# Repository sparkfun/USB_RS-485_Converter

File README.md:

SparkFun USB to RS-485 Converter
========================================

[*SparkFun USB to RS-485 Converter (BOB-09822)*](https://www.sparkfun.com/products/9822)

This breakout board pairs an SP3485 RS-485 transceiver with an FT232RL USB UART IC to convert a USB stream to RS-485.

Repository Contents
-------------------

* **/Hardware** - Eagle design files (.brd, .sch)
* **/Production** - Production panel files (.brd)

Documentation
--------------
* **[SparkFun Fritzing repo](https://github.com/sparkfun/Fritzing_Parts)** - Fritzing diagrams for SparkFun products.
* **[SparkFun 3D Model repo](https://github.com/sparkfun/3D_Models)** - 3D models of SparkFun products. 

License Information
-------------------
This product is _**open source**_! 

The **hardware** is released under [Creative Commons ShareAlike 4.0 International](https://creativecommons.org/licenses/by-sa/4.0/).

Please use, reuse, and modify these files as you see fit. Please maintain attribution to SparkFun Electronics and release anything derivative under the same license.

Distributed as-is; no warranty is given.

- Your friends at SparkFun.

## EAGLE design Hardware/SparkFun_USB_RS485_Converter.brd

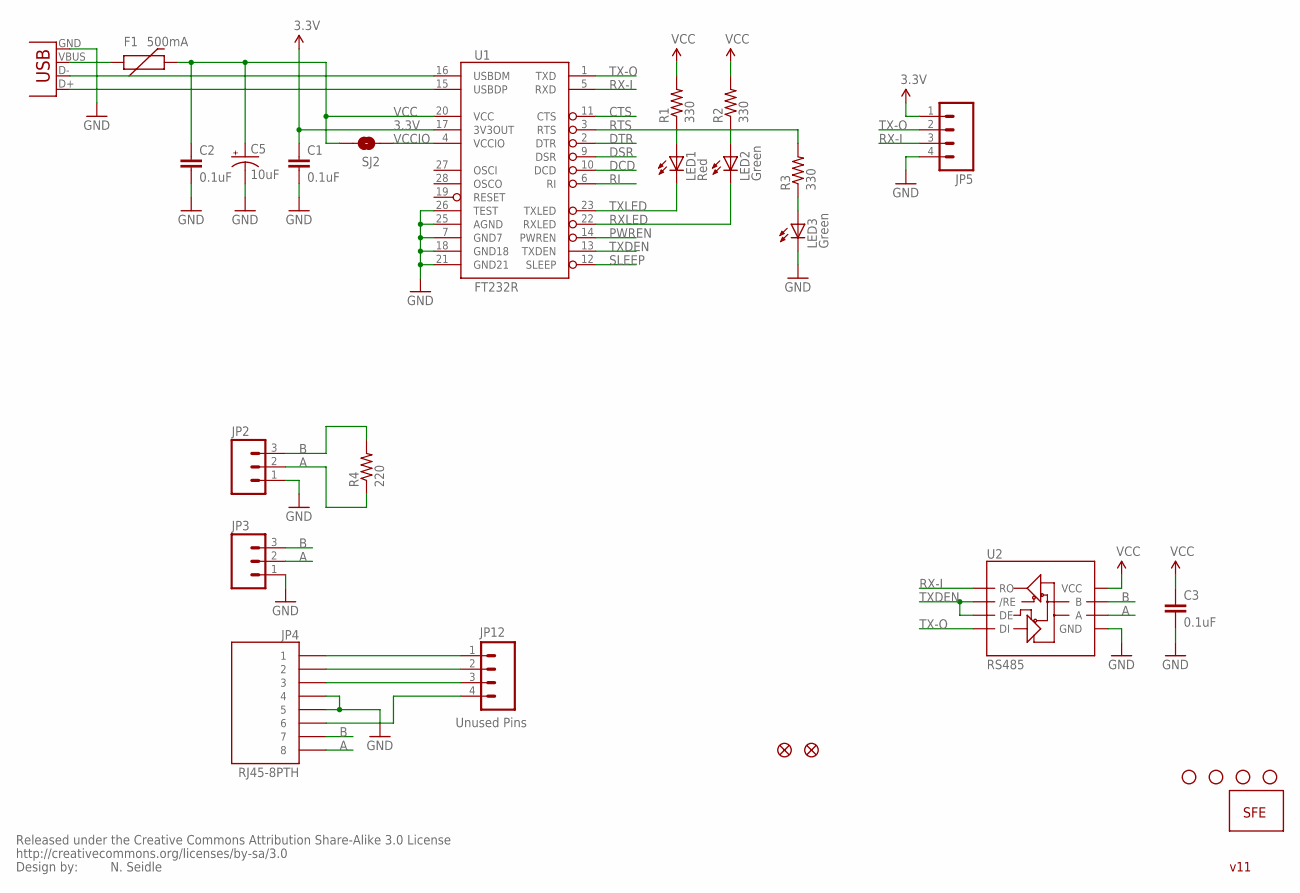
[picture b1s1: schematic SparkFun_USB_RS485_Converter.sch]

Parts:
C1, C2, C3: 0.1uF; 0402-CAP
C5: 10uF; EIA3216
F1: 500mA; PTC-1206
JP1, JP6, JP7, JP8: STAND-OFF
JP2: M03SCREW; SCREWTERMINAL-3.5MM-3
JP3: M03PTH; 1X03
JP4: RJ45-8PTH; RJ45-8
JP5: M04PTH; 1X04
JP9, JP10: FIDUCIAL1X2; FIDUCIAL-1X2
JP12: Unused Pins; 1X04
LED1: Red; LED-0603
LED2, LED3: Green; LED-0603
R1, R2, R3: 330; 0402-RES
R4: 220; 0402-RES
SJ2: SOLDERJUMPERNC2; SJ_2S-NOTRACE
U1: FT232R; SSOP28DB
U2: RS485; SO08
U$1: CREATIVE_COMMONS
U$2: LOGO-SFENEW; SFE-NEW-WEBLOGO
X2: USBSMD; USB-MINIB

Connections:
3.3V: C1.1, JP5.1, U1.17 (3V3OUT)
A: JP2.2, JP3.2, JP4.8, R4.1, U2.6 (A)
B: JP2.3, JP3.3, JP4.7, R4.2, U2.7 (B)
CTS: U1.11 (CTS)
DCD: U1.10 (DCD)
DSR: U1.9 (DSR)
DTR: U1.2 (DTR)
GND: C1.2, C2.2, C3.2, C5.C (-), JP2.1, JP3.1, JP4.4, JP4.5, JP5.4, LED3.C, U1.7 (GND7), U1.18 (GND18), U1.21 (GND21), U1.25 (AGND), U1.26 (TEST), U2.5 (GND), X2.GND
unnamed: LED1.A, R1.1
unnamed: LED2.A, R2.1
unnamed: F1.1, X2.VBUS
unnamed: LED3.A, R3.1
unnamed: JP4.1, JP12.1
unnamed: JP4.2, JP12.2
unnamed: JP4.3, JP12.3
unnamed: JP4.6, JP12.4
PWREN: U1.14 (PWREN)
RI: U1.6 (RI)
RTS: R3.2, U1.3 (RTS)
RX-I: JP5.3, U1.5 (RXD), U2.1 (RO)
RXLED: LED2.C, U1.22 (RXLED)
SLEEP: U1.12 (SLEEP)
TX-O: JP5.2, U1.1 (TXD), U2.4 (DI)
TXDEN: U1.13 (TXDEN), U2.2 (/RE), U2.3 (DE)
TXLED: LED1.C, U1.23 (TXLED)
USB_D+: U1.15 (USBDP), X2.D+
USB_D-: U1.16 (USBDM), X2.D-
VCC: C2.1, C3.1, C5.A (+), F1.2, R1.2, R2.2, SJ2.2, U1.20 (VCC), U2.8 (VCC)
VCCIO: SJ2.1, U1.4 (VCCIO)

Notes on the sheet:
N. Seidle
v11

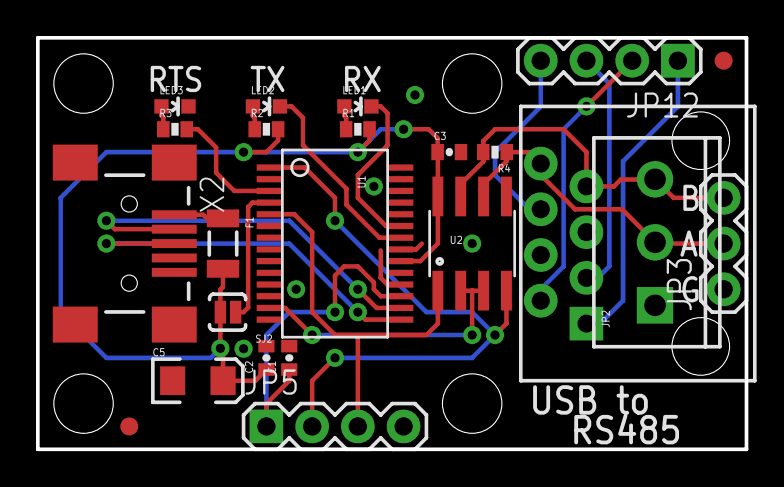
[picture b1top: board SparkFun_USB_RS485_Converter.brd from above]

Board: 2 copper layers, 39.4 x 22.9 mm, 29 parts (1 on the bottom side), 22 nets.

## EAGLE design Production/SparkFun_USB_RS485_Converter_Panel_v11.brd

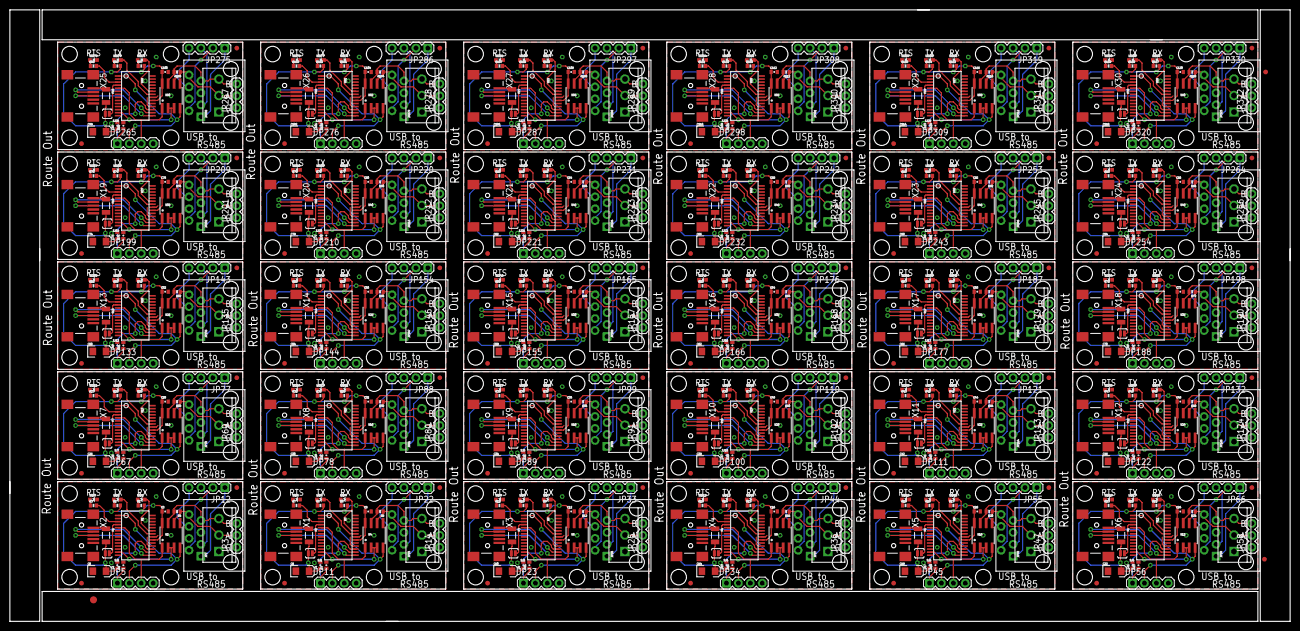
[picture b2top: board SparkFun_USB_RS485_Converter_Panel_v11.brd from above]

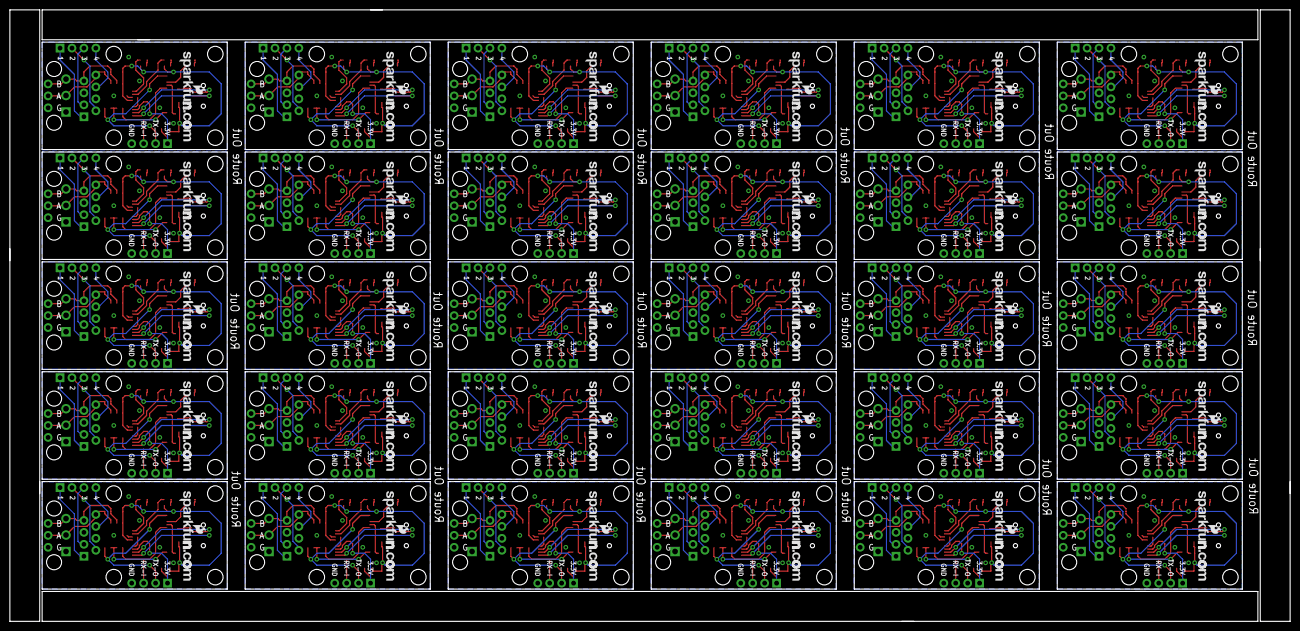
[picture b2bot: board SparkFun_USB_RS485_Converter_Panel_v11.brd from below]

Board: 2 copper layers, 272.3 x 130.0 mm, 843 parts (30 on the bottom side), 660 nets.

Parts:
C1, C2, C3, C4, C7, C8, C9, C11, C12, C13, C15, C16, C17, C19, C20, C21, C23, C24, C25, C27, C28, C29, C31, C32, C33, C35, C36, C37, C39, C40, C41, C43, C44, C45, C47, C48, C49, C51, C52, C53, C55, C56, C57, C59, C60, C61, C63, C64, C65, C67, C68, C69, C71, C72, C73, C75, C76, C77, C79, C80, C81, C83, C84, C85, C87, C88, C89, C91, C92, C93, C95, C96, C97, C99, C100, C101, C103, C104, C105, C107, C108, C109, C111, C112, C113, C115, C116, C117, C119, C120: 0.1uF; 0402-CAP
C5, C6, C10, C14, C18, C22, C26, C30, C34, C38, C42, C46, C50, C54, C58, C62, C66, C70, C74, C78, C82, C86, C90, C94, C98, C102, C106, C110, C114, C118: 10uF; EIA3216
E$1: FIDUCIAL-1.5X3
E$5, E$6: FIDUCIAL-1X2
F1, F2, F3, F4, F5, F6, F7, F8, F9, F10, F11, F12, F13, F14, F15, F16, F17, F18, F19, F20, F21, F22, F23, F24, F25, F26, F27, F28, F29, F30: 500mA; PTC-1206
JP1, JP6, JP7, JP8, JP16, JP17, JP18, JP19, JP27, JP28, JP29, JP30, JP38, JP39, JP40, JP41, JP49, JP50, JP51, JP52, JP60, JP61, JP62, JP63, JP71, JP72, JP73, JP74, JP82, JP83, JP84, JP85, JP93, JP94, JP95, JP96, JP104, JP105, JP106, JP107, JP115, JP116, JP117, JP118, JP126, JP127, JP128, JP129, JP137, JP138, JP139, JP140, JP148, JP149, JP150, JP151, JP159, JP160, JP161, JP162, JP170, JP171, JP172, JP173, JP181, JP182, JP183, JP184, JP192, JP193, JP194, JP195, JP203, JP204, JP205, JP206, JP214, JP215, JP216, JP217, JP225, JP226, JP227, JP228, JP236, JP237, JP238, JP239, JP247, JP248, JP249, JP250, JP258, JP259, JP260, JP261, JP269, JP270, JP271, JP272, JP280, JP281, JP282, JP283, JP291, JP292, JP293, JP294, JP302, JP303, JP304, JP305, JP313, JP314, JP315, JP316, JP324, JP325, JP326, JP327: STAND-OFF
JP2, JP15, JP26, JP37, JP48, JP59, JP70, JP81, JP92, JP103, JP114, JP125, JP136, JP147, JP158, JP169, JP180, JP191, JP202, JP213, JP224, JP235, JP246, JP257, JP268, JP279, JP290, JP301, JP312, JP323: SCREWTERMINAL-3.5MM-3
JP3, JP14, JP25, JP36, JP47, JP58, JP69, JP80, JP91, JP102, JP113, JP124, JP135, JP146, JP157, JP168, JP179, JP190, JP201, JP212, JP223, JP234, JP245, JP256, JP267, JP278, JP289, JP300, JP311, JP322: 1X03
JP4, JP13, JP24, JP35, JP46, JP57, JP68, JP79, JP90, JP101, JP112, JP123, JP134, JP145, JP156, JP167, JP178, JP189, JP200, JP211, JP222, JP233, JP244, JP255, JP266, JP277, JP288, JP299, JP310, JP321: RJ45-8PTH; RJ45-8
JP5, JP11, JP23, JP34, JP45, JP56, JP67, JP78, JP89, JP100, JP111, JP122, JP133, JP144, JP155, JP166, JP177, JP188, JP199, JP210, JP221, JP232, JP243, JP254, JP265, JP276, JP287, JP298, JP309, JP320: 1X04
JP9, JP10, JP20, JP21, JP31, JP32, JP42, JP43, JP53, JP54, JP64, JP65, JP75, JP76, JP86, JP87, JP97, JP98, JP108, JP109, JP119, JP120, JP130, JP131, JP141, JP142, JP152, JP153, JP163, JP164, JP174, JP175, JP185, JP186, JP196, JP197, JP207, JP208, JP218, JP219, JP229, JP230, JP240, JP241, JP251, JP252, JP262, JP263, JP273, JP274, JP284, JP285, JP295, JP296, JP306, JP307, JP317, JP318, JP328, JP329: FIDUCIAL1X2; FIDUCIAL-1X2
JP12, JP22, JP33, JP44, JP55, JP66, JP77, JP88, JP99, JP110, JP121, JP132, JP143, JP154, JP165, JP176, JP187, JP198, JP209, JP220, JP231, JP242, JP253, JP264, JP275, JP286, JP297, JP308, JP319, JP330: Unused Pins; 1X04
LED1, LED4, LED7, LED10, LED13, LED16, LED19, LED22, LED25, LED28, LED31, LED34, LED37, LED40, LED43, LED46, LED49, LED52, LED55, LED58, LED61, LED64, LED67, LED70, LED73, LED76, LED79, LED82, LED85, LED88: Red; LED-0603
LED2, LED3, LED5, LED6, LED8, LED9, LED11, LED12, LED14, LED15, LED17, LED18, LED20, LED21, LED23, LED24, LED26, LED27, LED29, LED30, LED32, LED33, LED35, LED36, LED38, LED39, LED41, LED42, LED44, LED45, LED47, LED48, LED50, LED51, LED53, LED54, LED56, LED57, LED59, LED60, LED62, LED63, LED65, LED66, LED68, LED69, LED71, LED72, LED74, LED75, LED77, LED78, LED80, LED81, LED83, LED84, LED86, LED87, LED89, LED90: Green; LED-0603
R1, R2, R3, R5, R6, R7, R9, R10, R11, R13, R14, R15, R17, R18, R19, R21, R22, R23, R25, R26, R27, R29, R30, R31, R33, R34, R35, R37, R38, R39, R41, R42, R43, R45, R46, R47, R49, R50, R51, R53, R54, R55, R57, R58, R59, R61, R62, R63, R65, R66, R67, R69, R70, R71, R73, R74, R75, R77, R78, R79, R81, R82, R83, R85, R86, R87, R89, R90, R91, R93, R94, R95, R97, R98, R99, R101, R102, R103, R105, R106, R107, R109, R110, R111, R113, R114, R115, R117, R118, R119: 330; 0402-RES
R4, R8, R12, R16, R20, R24, R28, R32, R36, R40, R44, R48, R52, R56, R60, R64, R68, R72, R76, R80, R84, R88, R92, R96, R100, R104, R108, R112, R116, R120: 220; 0402-RES
SJ1, SJ2, SJ3, SJ4, SJ5, SJ6, SJ7, SJ8, SJ9, SJ10, SJ11, SJ12, SJ13, SJ14, SJ15, SJ16, SJ17, SJ18, SJ19, SJ20, SJ21, SJ22, SJ23, SJ24, SJ25, SJ26, SJ27, SJ28, SJ29, SJ30: SOLDERJUMPERNC2; SJ_2S-NOTRACE
U1, U3, U5, U7, U9, U11, U13, U15, U17, U19, U21, U23, U25, U27, U29, U31, U33, U35, U37, U39, U41, U43, U45, U47, U49, U51, U53, U55, U57, U59: FT232R; SSOP28DB
U2, U4, U6, U8, U10, U12, U14, U16, U18, U20, U22, U24, U26, U28, U30, U32, U34, U36, U38, U40, U42, U44, U46, U48, U50, U52, U54, U56, U58, U60: RS485; SO08
U$1, U$2, U$3, U$4, U$5, U$6, U$7, U$8, U$9, U$10, U$11, U$12, U$13, U$14, U$15, U$16, U$17, U$18, U$19, U$20, U$21, U$22, U$23, U$24, U$25, U$26, U$27, U$28, U$29, U$30: LOGO-SFENEW; SFE-NEW-WEBLOGO
X1, X2, X3, X4, X5, X6, X7, X8, X9, X10, X11, X12, X13, X14, X15, X16, X17, X18, X19, X20, X21, X22, X23, X24, X25, X26, X27, X28, X29, X30: USBSMD; USB-MINIB

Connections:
3.3V: C1.1, JP5.1, U1.17
3.3V1: C7.1, JP11.1, U3.17
3.3V2: C11.1, JP23.1, U5.17
3.3V3: C15.1, JP34.1, U7.17
3.3V4: C19.1, JP45.1, U9.17
3.3V5: C23.1, JP56.1, U11.17
3.3V6: C27.1, JP67.1, U13.17
3.3V7: C31.1, JP78.1, U15.17
3.3V8: C35.1, JP89.1, U17.17
3.3V9: C39.1, JP100.1, U19.17
3.3V10: C43.1, JP111.1, U21.17
3.3V11: C47.1, JP122.1, U23.17
3.3V12: C51.1, JP133.1, U25.17
3.3V13: C55.1, JP144.1, U27.17
3.3V14: C59.1, JP155.1, U29.17
3.3V15: C63.1, JP166.1, U31.17
3.3V16: C67.1, JP177.1, U33.17
3.3V17: C71.1, JP188.1, U35.17
3.3V18: C75.1, JP199.1, U37.17
3.3V19: C79.1, JP210.1, U39.17
3.3V20: C83.1, JP221.1, U41.17
3.3V21: C87.1, JP232.1, U43.17
3.3V22: C91.1, JP243.1, U45.17
3.3V23: C95.1, JP254.1, U47.17
3.3V24: C99.1, JP265.1, U49.17
3.3V25: C103.1, JP276.1, U51.17
3.3V26: C107.1, JP287.1, U53.17
3.3V27: C111.1, JP298.1, U55.17
3.3V28: C115.1, JP309.1, U57.17
3.3V29: C119.1, JP320.1, U59.17
A: JP2.2, JP3.2, JP4.8, R4.1, U2.6
A1: JP13.8, JP14.2, JP15.2, R8.1, U4.6
A2: JP24.8, JP25.2, JP26.2, R12.1, U6.6
A3: JP35.8, JP36.2, JP37.2, R16.1, U8.6
A4: JP46.8, JP47.2, JP48.2, R20.1, U10.6
A5: JP57.8, JP58.2, JP59.2, R24.1, U12.6
A6: JP68.8, JP69.2, JP70.2, R28.1, U14.6
A7: JP79.8, JP80.2, JP81.2, R32.1, U16.6
A8: JP90.8, JP91.2, JP92.2, R36.1, U18.6
A9: JP101.8, JP102.2, JP103.2, R40.1, U20.6
A10: JP112.8, JP113.2, JP114.2, R44.1, U22.6
A11: JP123.8, JP124.2, JP125.2, R48.1, U24.6
A12: JP134.8, JP135.2, JP136.2, R52.1, U26.6
A13: JP145.8, JP146.2, JP147.2, R56.1, U28.6
A14: JP156.8, JP157.2, JP158.2, R60.1, U30.6
A15: JP167.8, JP168.2, JP169.2, R64.1, U32.6
A16: JP178.8, JP179.2, JP180.2, R68.1, U34.6
A17: JP189.8, JP190.2, JP191.2, R72.1, U36.6
A18: JP200.8, JP201.2, JP202.2, R76.1, U38.6
A19: JP211.8, JP212.2, JP213.2, R80.1, U40.6
A20: JP222.8, JP223.2, JP224.2, R84.1, U42.6
A21: JP233.8, JP234.2, JP235.2, R88.1, U44.6
A22: JP244.8, JP245.2, JP246.2, R92.1, U46.6
A23: JP255.8, JP256.2, JP257.2, R96.1, U48.6
A24: JP266.8, JP267.2, JP268.2, R100.1, U50.6
A25: JP277.8, JP278.2, JP279.2, R104.1, U52.6
A26: JP288.8, JP289.2, JP290.2, R108.1, U54.6
A27: JP299.8, JP300.2, JP301.2, R112.1, U56.6
A28: JP310.8, JP311.2, JP312.2, R116.1, U58.6
A29: JP321.8, JP322.2, JP323.2, R120.1, U60.6
B: JP2.3, JP3.3, JP4.7, R4.2, U2.7
B1: JP13.7, JP14.3, JP15.3, R8.2, U4.7
B2: JP24.7, JP25.3, JP26.3, R12.2, U6.7
B3: JP35.7, JP36.3, JP37.3, R16.2, U8.7
B4: JP46.7, JP47.3, JP48.3, R20.2, U10.7
B5: JP57.7, JP58.3, JP59.3, R24.2, U12.7
B6: JP68.7, JP69.3, JP70.3, R28.2, U14.7
B7: JP79.7, JP80.3, JP81.3, R32.2, U16.7
B8: JP90.7, JP91.3, JP92.3, R36.2, U18.7
B9: JP101.7, JP102.3, JP103.3, R40.2, U20.7
B10: JP112.7, JP113.3, JP114.3, R44.2, U22.7
B11: JP123.7, JP124.3, JP125.3, R48.2, U24.7
B12: JP134.7, JP135.3, JP136.3, R52.2, U26.7
B13: JP145.7, JP146.3, JP147.3, R56.2, U28.7
B14: JP156.7, JP157.3, JP158.3, R60.2, U30.7
B15: JP167.7, JP168.3, JP169.3, R64.2, U32.7
B16: JP178.7, JP179.3, JP180.3, R68.2, U34.7
B17: JP189.7, JP190.3, JP191.3, R72.2, U36.7
B18: JP200.7, JP201.3, JP202.3, R76.2, U38.7
B19: JP211.7, JP212.3, JP213.3, R80.2, U40.7
B20: JP222.7, JP223.3, JP224.3, R84.2, U42.7
B21: JP233.7, JP234.3, JP235.3, R88.2, U44.7
B22: JP244.7, JP245.3, JP246.3, R92.2, U46.7
B23: JP255.7, JP256.3, JP257.3, R96.2, U48.7
B24: JP266.7, JP267.3, JP268.3, R100.2, U50.7
B25: JP277.7, JP278.3, JP279.3, R104.2, U52.7
B26: JP288.7, JP289.3, JP290.3, R108.2, U54.7
B27: JP299.7, JP300.3, JP301.3, R112.2, U56.7
B28: JP310.7, JP311.3, JP312.3, R116.2, U58.7
B29: JP321.7, JP322.3, JP323.3, R120.2, U60.7
GND: C1.2, C2.2, C3.2, C5.C, JP2.1, JP3.1, JP4.4, JP4.5, JP5.4, LED3.C, U1.7, U1.18, U1.21, U1.25, U1.26, U2.5, X2.GND
GND1: C4.2, C6.C, C7.2, C8.2, JP11.4, JP13.4, JP13.5, JP14.1, JP15.1, LED6.C, U3.7, U3.18, U3.21, U3.25, U3.26, U4.5, X1.GND
GND2: C9.2, C10.C, C11.2, C12.2, JP23.4, JP24.4, JP24.5, JP25.1, JP26.1, LED9.C, U5.7, U5.18, U5.21, U5.25, U5.26, U6.5, X3.GND
GND3: C13.2, C14.C, C15.2, C16.2, JP34.4, JP35.4, JP35.5, JP36.1, JP37.1, LED12.C, U7.7, U7.18, U7.21, U7.25, U7.26, U8.5, X4.GND
GND4: C17.2, C18.C, C19.2, C20.2, JP45.4, JP46.4, JP46.5, JP47.1, JP48.1, LED15.C, U9.7, U9.18, U9.21, U9.25, U9.26, U10.5, X5.GND
GND5: C21.2, C22.C, C23.2, C24.2, JP56.4, JP57.4, JP57.5, JP58.1, JP59.1, LED18.C, U11.7, U11.18, U11.21, U11.25, U11.26, U12.5, X6.GND
GND6: C25.2, C26.C, C27.2, C28.2, JP67.4, JP68.4, JP68.5, JP69.1, JP70.1, LED21.C, U13.7, U13.18, U13.21, U13.25, U13.26, U14.5, X7.GND
GND7: C29.2, C30.C, C31.2, C32.2, JP78.4, JP79.4, JP79.5, JP80.1, JP81.1, LED24.C, U15.7, U15.18, U15.21, U15.25, U15.26, U16.5, X8.GND
GND8: C33.2, C34.C, C35.2, C36.2, JP89.4, JP90.4, JP90.5, JP91.1, JP92.1, LED27.C, U17.7, U17.18, U17.21, U17.25, U17.26, U18.5, X9.GND
GND9: C37.2, C38.C, C39.2, C40.2, JP100.4, JP101.4, JP101.5, JP102.1, JP103.1, LED30.C, U19.7, U19.18, U19.21, U19.25, U19.26, U20.5, X10.GND
GND10: C41.2, C42.C, C43.2, C44.2, JP111.4, JP112.4, JP112.5, JP113.1, JP114.1, LED33.C, U21.7, U21.18, U21.21, U21.25, U21.26, U22.5, X11.GND
GND11: C45.2, C46.C, C47.2, C48.2, JP122.4, JP123.4, JP123.5, JP124.1, JP125.1, LED36.C, U23.7, U23.18, U23.21, U23.25, U23.26, U24.5, X12.GND
GND12: C49.2, C50.C, C51.2, C52.2, JP133.4, JP134.4, JP134.5, JP135.1, JP136.1, LED39.C, U25.7, U25.18, U25.21, U25.25, U25.26, U26.5, X13.GND
GND13: C53.2, C54.C, C55.2, C56.2, JP144.4, JP145.4, JP145.5, JP146.1, JP147.1, LED42.C, U27.7, U27.18, U27.21, U27.25, U27.26, U28.5, X14.GND
GND14: C57.2, C58.C, C59.2, C60.2, JP155.4, JP156.4, JP156.5, JP157.1, JP158.1, LED45.C, U29.7, U29.18, U29.21, U29.25, U29.26, U30.5, X15.GND
GND15: C61.2, C62.C, C63.2, C64.2, JP166.4, JP167.4, JP167.5, JP168.1, JP169.1, LED48.C, U31.7, U31.18, U31.21, U31.25, U31.26, U32.5, X16.GND
GND16: C65.2, C66.C, C67.2, C68.2, JP177.4, JP178.4, JP178.5, JP179.1, JP180.1, LED51.C, U33.7, U33.18, U33.21, U33.25, U33.26, U34.5, X17.GND
GND17: C69.2, C70.C, C71.2, C72.2, JP188.4, JP189.4, JP189.5, JP190.1, JP191.1, LED54.C, U35.7, U35.18, U35.21, U35.25, U35.26, U36.5, X18.GND
GND18: C73.2, C74.C, C75.2, C76.2, JP199.4, JP200.4, JP200.5, JP201.1, JP202.1, LED57.C, U37.7, U37.18, U37.21, U37.25, U37.26, U38.5, X19.GND
GND19: C77.2, C78.C, C79.2, C80.2, JP210.4, JP211.4, JP211.5, JP212.1, JP213.1, LED60.C, U39.7, U39.18, U39.21, U39.25, U39.26, U40.5, X20.GND
GND20: C81.2, C82.C, C83.2, C84.2, JP221.4, JP222.4, JP222.5, JP223.1, JP224.1, LED63.C, U41.7, U41.18, U41.21, U41.25, U41.26, U42.5, X21.GND
GND21: C85.2, C86.C, C87.2, C88.2, JP232.4, JP233.4, JP233.5, JP234.1, JP235.1, LED66.C, U43.7, U43.18, U43.21, U43.25, U43.26, U44.5, X22.GND
GND22: C89.2, C90.C, C91.2, C92.2, JP243.4, JP244.4, JP244.5, JP245.1, JP246.1, LED69.C, U45.7, U45.18, U45.21, U45.25, U45.26, U46.5, X23.GND
GND23: C93.2, C94.C, C95.2, C96.2, JP254.4, JP255.4, JP255.5, JP256.1, JP257.1, LED72.C, U47.7, U47.18, U47.21, U47.25, U47.26, U48.5, X24.GND
GND24: C97.2, C98.C, C99.2, C100.2, JP265.4, JP266.4, JP266.5, JP267.1, JP268.1, LED75.C, U49.7, U49.18, U49.21, U49.25, U49.26, U50.5, X25.GND
GND25: C101.2, C102.C, C103.2, C104.2, JP276.4, JP277.4, JP277.5, JP278.1, JP279.1, LED78.C, U51.7, U51.18, U51.21, U51.25, U51.26, U52.5, X26.GND
GND26: C105.2, C106.C, C107.2, C108.2, JP287.4, JP288.4, JP288.5, JP289.1, JP290.1, LED81.C, U53.7, U53.18, U53.21, U53.25, U53.26, U54.5, X27.GND
GND27: C109.2, C110.C, C111.2, C112.2, JP298.4, JP299.4, JP299.5, JP300.1, JP301.1, LED84.C, U55.7, U55.18, U55.21, U55.25, U55.26, U56.5, X28.GND
GND28: C113.2, C114.C, C115.2, C116.2, JP309.4, JP310.4, JP310.5, JP311.1, JP312.1, LED87.C, U57.7, U57.18, U57.21, U57.25, U57.26, U58.5, X29.GND
GND29: C117.2, C118.C, C119.2, C120.2, JP320.4, JP321.4, JP321.5, JP322.1, JP323.1, LED90.C, U59.7, U59.18, U59.21, U59.25, U59.26, U60.5, X30.GND
unnamed: LED1.A, R1.1
unnamed: LED2.A, R2.1
unnamed: F1.1, X2.VBUS
unnamed: LED3.A, R3.1
unnamed: JP4.1, JP12.1
unnamed: JP4.2, JP12.2
unnamed: JP4.3, JP12.3
unnamed: JP4.6, JP12.4
unnamed: LED4.A, R5.1
unnamed: LED5.A, R6.1
unnamed: F2.1, X1.VBUS
unnamed: LED6.A, R7.1
unnamed: JP13.1, JP22.1
unnamed: JP13.2, JP22.2
unnamed: JP13.3, JP22.3
unnamed: JP13.6, JP22.4
unnamed: LED7.A, R9.1
unnamed: LED8.A, R10.1
unnamed: F3.1, X3.VBUS
unnamed: LED9.A, R11.1
unnamed: JP24.1, JP33.1
unnamed: JP24.2, JP33.2
unnamed: JP24.3, JP33.3
unnamed: JP24.6, JP33.4
unnamed: LED10.A, R13.1
unnamed: LED11.A, R14.1
unnamed: F4.1, X4.VBUS
unnamed: LED12.A, R15.1
unnamed: JP35.1, JP44.1
unnamed: JP35.2, JP44.2
unnamed: JP35.3, JP44.3
unnamed: JP35.6, JP44.4
unnamed: LED13.A, R17.1
unnamed: LED14.A, R18.1
unnamed: F5.1, X5.VBUS
unnamed: LED15.A, R19.1
unnamed: JP46.1, JP55.1
unnamed: JP46.2, JP55.2
unnamed: JP46.3, JP55.3
unnamed: JP46.6, JP55.4
unnamed: LED16.A, R21.1
unnamed: LED17.A, R22.1
unnamed: F6.1, X6.VBUS
unnamed: LED18.A, R23.1
unnamed: JP57.1, JP66.1
unnamed: JP57.2, JP66.2
unnamed: JP57.3, JP66.3
unnamed: JP57.6, JP66.4
unnamed: LED19.A, R25.1
unnamed: LED20.A, R26.1
unnamed: F7.1, X7.VBUS
unnamed: LED21.A, R27.1
unnamed: JP68.1, JP77.1
unnamed: JP68.2, JP77.2
unnamed: JP68.3, JP77.3
unnamed: JP68.6, JP77.4
unnamed: LED22.A, R29.1
unnamed: LED23.A, R30.1
unnamed: F8.1, X8.VBUS
unnamed: LED24.A, R31.1
unnamed: JP79.1, JP88.1
unnamed: JP79.2, JP88.2
unnamed: JP79.3, JP88.3
unnamed: JP79.6, JP88.4
unnamed: LED25.A, R33.1
unnamed: LED26.A, R34.1
unnamed: F9.1, X9.VBUS
unnamed: LED27.A, R35.1
unnamed: JP90.1, JP99.1
unnamed: JP90.2, JP99.2
unnamed: JP90.3, JP99.3
unnamed: JP90.6, JP99.4
unnamed: LED28.A, R37.1
unnamed: LED29.A, R38.1
unnamed: F10.1, X10.VBUS
unnamed: LED30.A, R39.1
unnamed: JP101.1, JP110.1
unnamed: JP101.2, JP110.2
unnamed: JP101.3, JP110.3
unnamed: JP101.6, JP110.4
unnamed: LED31.A, R41.1
unnamed: LED32.A, R42.1
unnamed: F11.1, X11.VBUS
unnamed: LED33.A, R43.1
unnamed: JP112.1, JP121.1
unnamed: JP112.2, JP121.2
unnamed: JP112.3, JP121.3
unnamed: JP112.6, JP121.4
unnamed: LED34.A, R45.1
unnamed: LED35.A, R46.1
unnamed: F12.1, X12.VBUS
unnamed: LED36.A, R47.1
unnamed: JP123.1, JP132.1
unnamed: JP123.2, JP132.2
unnamed: JP123.3, JP132.3
unnamed: JP123.6, JP132.4
unnamed: LED37.A, R49.1
unnamed: LED38.A, R50.1
unnamed: F13.1, X13.VBUS
unnamed: LED39.A, R51.1
unnamed: JP134.1, JP143.1
unnamed: JP134.2, JP143.2
unnamed: JP134.3, JP143.3
unnamed: JP134.6, JP143.4
unnamed: LED40.A, R53.1
unnamed: LED41.A, R54.1
unnamed: F14.1, X14.VBUS
unnamed: LED42.A, R55.1
unnamed: JP145.1, JP154.1
unnamed: JP145.2, JP154.2
unnamed: JP145.3, JP154.3
unnamed: JP145.6, JP154.4
unnamed: LED43.A, R57.1
unnamed: LED44.A, R58.1
unnamed: F15.1, X15.VBUS
unnamed: LED45.A, R59.1
unnamed: JP156.1, JP165.1
unnamed: JP156.2, JP165.2
unnamed: JP156.3, JP165.3
unnamed: JP156.6, JP165.4
unnamed: LED46.A, R61.1
unnamed: LED47.A, R62.1
unnamed: F16.1, X16.VBUS
unnamed: LED48.A, R63.1
unnamed: JP167.1, JP176.1
unnamed: JP167.2, JP176.2
unnamed: JP167.3, JP176.3
unnamed: JP167.6, JP176.4
unnamed: LED49.A, R65.1
unnamed: LED50.A, R66.1
unnamed: F17.1, X17.VBUS
unnamed: LED51.A, R67.1
unnamed: JP178.1, JP187.1
unnamed: JP178.2, JP187.2
unnamed: JP178.3, JP187.3
unnamed: JP178.6, JP187.4
unnamed: LED52.A, R69.1
unnamed: LED53.A, R70.1
unnamed: F18.1, X18.VBUS
unnamed: LED54.A, R71.1
unnamed: JP189.1, JP198.1
unnamed: JP189.2, JP198.2
unnamed: JP189.3, JP198.3
unnamed: JP189.6, JP198.4
unnamed: LED55.A, R73.1
unnamed: LED56.A, R74.1
unnamed: F19.1, X19.VBUS
unnamed: LED57.A, R75.1
unnamed: JP200.1, JP209.1
unnamed: JP200.2, JP209.2
unnamed: JP200.3, JP209.3
unnamed: JP200.6, JP209.4
unnamed: LED58.A, R77.1
unnamed: LED59.A, R78.1
unnamed: F20.1, X20.VBUS
unnamed: LED60.A, R79.1
unnamed: JP211.1, JP220.1
unnamed: JP211.2, JP220.2
unnamed: JP211.3, JP220.3
unnamed: JP211.6, JP220.4
unnamed: LED61.A, R81.1
unnamed: LED62.A, R82.1
unnamed: F21.1, X21.VBUS
unnamed: LED63.A, R83.1
unnamed: JP222.1, JP231.1
unnamed: JP222.2, JP231.2
unnamed: JP222.3, JP231.3
unnamed: JP222.6, JP231.4
unnamed: LED64.A, R85.1
unnamed: LED65.A, R86.1
unnamed: F22.1, X22.VBUS
unnamed: LED66.A, R87.1
unnamed: JP233.1, JP242.1
unnamed: JP233.2, JP242.2
unnamed: JP233.3, JP242.3
unnamed: JP233.6, JP242.4
unnamed: LED67.A, R89.1
unnamed: LED68.A, R90.1
unnamed: F23.1, X23.VBUS
unnamed: LED69.A, R91.1
unnamed: JP244.1, JP253.1
unnamed: JP244.2, JP253.2
unnamed: JP244.3, JP253.3
unnamed: JP244.6, JP253.4
unnamed: LED70.A, R93.1
unnamed: LED71.A, R94.1
unnamed: F24.1, X24.VBUS
unnamed: LED72.A, R95.1
unnamed: JP255.1, JP264.1
unnamed: JP255.2, JP264.2
unnamed: JP255.3, JP264.3
unnamed: JP255.6, JP264.4
unnamed: LED73.A, R97.1
unnamed: LED74.A, R98.1
unnamed: F25.1, X25.VBUS
unnamed: LED75.A, R99.1
unnamed: JP266.1, JP275.1
unnamed: JP266.2, JP275.2
unnamed: JP266.3, JP275.3
unnamed: JP266.6, JP275.4
unnamed: LED76.A, R101.1
unnamed: LED77.A, R102.1
unnamed: F26.1, X26.VBUS
unnamed: LED78.A, R103.1
unnamed: JP277.1, JP286.1
unnamed: JP277.2, JP286.2
unnamed: JP277.3, JP286.3
unnamed: JP277.6, JP286.4
unnamed: LED79.A, R105.1
unnamed: LED80.A, R106.1
unnamed: F27.1, X27.VBUS
unnamed: LED81.A, R107.1
unnamed: JP288.1, JP297.1
unnamed: JP288.2, JP297.2
unnamed: JP288.3, JP297.3
unnamed: JP288.6, JP297.4
unnamed: LED82.A, R109.1
unnamed: LED83.A, R110.1
unnamed: F28.1, X28.VBUS
unnamed: LED84.A, R111.1
unnamed: JP299.1, JP308.1
unnamed: JP299.2, JP308.2
unnamed: JP299.3, JP308.3
unnamed: JP299.6, JP308.4
unnamed: LED85.A, R113.1
unnamed: LED86.A, R114.1
unnamed: F29.1, X29.VBUS
unnamed: LED87.A, R115.1
unnamed: JP310.1, JP319.1
unnamed: JP310.2, JP319.2
unnamed: JP310.3, JP319.3
unnamed: JP310.6, JP319.4
unnamed: LED88.A, R117.1
unnamed: LED89.A, R118.1
unnamed: F30.1, X30.VBUS
unnamed: LED90.A, R119.1
unnamed: JP321.1, JP330.1
unnamed: JP321.2, JP330.2
unnamed: JP321.3, JP330.3
unnamed: JP321.6, JP330.4
RTS: R3.2, U1.3
RTS1: R7.2, U3.3
RTS2: R11.2, U5.3
RTS3: R15.2, U7.3
RTS4: R19.2, U9.3
RTS5: R23.2, U11.3
RTS6: R27.2, U13.3
RTS7: R31.2, U15.3
RTS8: R35.2, U17.3
RTS9: R39.2, U19.3
RTS10: R43.2, U21.3
RTS11: R47.2, U23.3
RTS12: R51.2, U25.3
RTS13: R55.2, U27.3
RTS14: R59.2, U29.3
RTS15: R63.2, U31.3
RTS16: R67.2, U33.3
RTS17: R71.2, U35.3
RTS18: R75.2, U37.3
RTS19: R79.2, U39.3
RTS20: R83.2, U41.3
RTS21: R87.2, U43.3
RTS22: R91.2, U45.3
RTS23: R95.2, U47.3
RTS24: R99.2, U49.3
RTS25: R103.2, U51.3
RTS26: R107.2, U53.3
RTS27: R111.2, U55.3
RTS28: R115.2, U57.3
RTS29: R119.2, U59.3
RX-I: JP5.3, U1.5, U2.1
RX-I1: JP11.3, U3.5, U4.1
RX-I2: JP23.3, U5.5, U6.1
RX-I3: JP34.3, U7.5, U8.1
RX-I4: JP45.3, U9.5, U10.1
RX-I5: JP56.3, U11.5, U12.1
RX-I6: JP67.3, U13.5, U14.1
RX-I7: JP78.3, U15.5, U16.1
RX-I8: JP89.3, U17.5, U18.1
RX-I9: JP100.3, U19.5, U20.1
RX-I10: JP111.3, U21.5, U22.1
RX-I11: JP122.3, U23.5, U24.1
RX-I12: JP133.3, U25.5, U26.1
RX-I13: JP144.3, U27.5, U28.1
RX-I14: JP155.3, U29.5, U30.1
RX-I15: JP166.3, U31.5, U32.1
RX-I16: JP177.3, U33.5, U34.1
RX-I17: JP188.3, U35.5, U36.1
RX-I18: JP199.3, U37.5, U38.1
RX-I19: JP210.3, U39.5, U40.1
RX-I20: JP221.3, U41.5, U42.1
RX-I21: JP232.3, U43.5, U44.1
RX-I22: JP243.3, U45.5, U46.1
RX-I23: JP254.3, U47.5, U48.1
RX-I24: JP265.3, U49.5, U50.1
RX-I25: JP276.3, U51.5, U52.1
RX-I26: JP287.3, U53.5, U54.1
RX-I27: JP298.3, U55.5, U56.1
RX-I28: JP309.3, U57.5, U58.1
RX-I29: JP320.3, U59.5, U60.1
RXLED: LED2.C, U1.22
RXLED1: LED5.C, U3.22
RXLED2: LED8.C, U5.22
RXLED3: LED11.C, U7.22
RXLED4: LED14.C, U9.22
RXLED5: LED17.C, U11.22
RXLED6: LED20.C, U13.22
RXLED7: LED23.C, U15.22
RXLED8: LED26.C, U17.22
RXLED9: LED29.C, U19.22
RXLED10: LED32.C, U21.22
RXLED11: LED35.C, U23.22
RXLED12: LED38.C, U25.22
RXLED13: LED41.C, U27.22
RXLED14: LED44.C, U29.22
RXLED15: LED47.C, U31.22
RXLED16: LED50.C, U33.22
RXLED17: LED53.C, U35.22
RXLED18: LED56.C, U37.22
RXLED19: LED59.C, U39.22
RXLED20: LED62.C, U41.22
RXLED21: LED65.C, U43.22
RXLED22: LED68.C, U45.22
RXLED23: LED71.C, U47.22
RXLED24: LED74.C, U49.22
RXLED25: LED77.C, U51.22
RXLED26: LED80.C, U53.22
RXLED27: LED83.C, U55.22
RXLED28: LED86.C, U57.22
RXLED29: LED89.C, U59.22
TX-O: JP5.2, U1.1, U2.4
TX-O1: JP11.2, U3.1, U4.4
TX-O2: JP23.2, U5.1, U6.4
TX-O3: JP34.2, U7.1, U8.4
TX-O4: JP45.2, U9.1, U10.4
TX-O5: JP56.2, U11.1, U12.4
TX-O6: JP67.2, U13.1, U14.4
TX-O7: JP78.2, U15.1, U16.4
TX-O8: JP89.2, U17.1, U18.4
TX-O9: JP100.2, U19.1, U20.4
TX-O10: JP111.2, U21.1, U22.4
TX-O11: JP122.2, U23.1, U24.4
TX-O12: JP133.2, U25.1, U26.4
TX-O13: JP144.2, U27.1, U28.4
TX-O14: JP155.2, U29.1, U30.4
TX-O15: JP166.2, U31.1, U32.4
TX-O16: JP177.2, U33.1, U34.4
TX-O17: JP188.2, U35.1, U36.4
TX-O18: JP199.2, U37.1, U38.4
TX-O19: JP210.2, U39.1, U40.4
TX-O20: JP221.2, U41.1, U42.4
TX-O21: JP232.2, U43.1, U44.4
TX-O22: JP243.2, U45.1, U46.4
TX-O23: JP254.2, U47.1, U48.4
TX-O24: JP265.2, U49.1, U50.4
TX-O25: JP276.2, U51.1, U52.4
TX-O26: JP287.2, U53.1, U54.4
TX-O27: JP298.2, U55.1, U56.4
TX-O28: JP309.2, U57.1, U58.4
TX-O29: JP320.2, U59.1, U60.4
TXDEN: U1.13, U2.2, U2.3
TXDEN1: U3.13, U4.2, U4.3
TXDEN2: U5.13, U6.2, U6.3
TXDEN3: U7.13, U8.2, U8.3
TXDEN4: U9.13, U10.2, U10.3
TXDEN5: U11.13, U12.2, U12.3
TXDEN6: U13.13, U14.2, U14.3
TXDEN7: U15.13, U16.2, U16.3
TXDEN8: U17.13, U18.2, U18.3
TXDEN9: U19.13, U20.2, U20.3
TXDEN10: U21.13, U22.2, U22.3
TXDEN11: U23.13, U24.2, U24.3
TXDEN12: U25.13, U26.2, U26.3
TXDEN13: U27.13, U28.2, U28.3
TXDEN14: U29.13, U30.2, U30.3
TXDEN15: U31.13, U32.2, U32.3
TXDEN16: U33.13, U34.2, U34.3
TXDEN17: U35.13, U36.2, U36.3
TXDEN18: U37.13, U38.2, U38.3
TXDEN19: U39.13, U40.2, U40.3
TXDEN20: U41.13, U42.2, U42.3
TXDEN21: U43.13, U44.2, U44.3
TXDEN22: U45.13, U46.2, U46.3
TXDEN23: U47.13, U48.2, U48.3
TXDEN24: U49.13, U50.2, U50.3
TXDEN25: U51.13, U52.2, U52.3
TXDEN26: U53.13, U54.2, U54.3
TXDEN27: U55.13, U56.2, U56.3
TXDEN28: U57.13, U58.2, U58.3
TXDEN29: U59.13, U60.2, U60.3
TXLED: LED1.C, U1.23
TXLED1: LED4.C, U3.23
TXLED2: LED7.C, U5.23
TXLED3: LED10.C, U7.23
TXLED4: LED13.C, U9.23
TXLED5: LED16.C, U11.23
TXLED6: LED19.C, U13.23
TXLED7: LED22.C, U15.23
TXLED8: LED25.C, U17.23
TXLED9: LED28.C, U19.23
TXLED10: LED31.C, U21.23
TXLED11: LED34.C, U23.23
TXLED12: LED37.C, U25.23
TXLED13: LED40.C, U27.23
TXLED14: LED43.C, U29.23
TXLED15: LED46.C, U31.23
TXLED16: LED49.C, U33.23
TXLED17: LED52.C, U35.23
TXLED18: LED55.C, U37.23
TXLED19: LED58.C, U39.23
TXLED20: LED61.C, U41.23
TXLED21: LED64.C, U43.23
TXLED22: LED67.C, U45.23
TXLED23: LED70.C, U47.23
TXLED24: LED73.C, U49.23
TXLED25: LED76.C, U51.23
TXLED26: LED79.C, U53.23
TXLED27: LED82.C, U55.23
TXLED28: LED85.C, U57.23
TXLED29: LED88.C, U59.23
USB_D+: U1.15, X2.D+
USB_D+1: U3.15, X1.D+
USB_D+2: U5.15, X3.D+
USB_D+3: U7.15, X4.D+
USB_D+4: U9.15, X5.D+
USB_D+5: U11.15, X6.D+
USB_D+6: U13.15, X7.D+
USB_D+7: U15.15, X8.D+
USB_D+8: U17.15, X9.D+
USB_D+9: U19.15, X10.D+
USB_D+10: U21.15, X11.D+
USB_D+11: U23.15, X12.D+
USB_D+12: U25.15, X13.D+
USB_D+13: U27.15, X14.D+
USB_D+14: U29.15, X15.D+
USB_D+15: U31.15, X16.D+
USB_D+16: U33.15, X17.D+
USB_D+17: U35.15, X18.D+
USB_D+18: U37.15, X19.D+
USB_D+19: U39.15, X20.D+
USB_D+20: U41.15, X21.D+
USB_D+21: U43.15, X22.D+
USB_D+22: U45.15, X23.D+
USB_D+23: U47.15, X24.D+
USB_D+24: U49.15, X25.D+
USB_D+25: U51.15, X26.D+
USB_D+26: U53.15, X27.D+
USB_D+27: U55.15, X28.D+
USB_D+28: U57.15, X29.D+
USB_D+29: U59.15, X30.D+
USB_D-: U1.16, X2.D-
USB_D-1: U3.16, X1.D-
USB_D-2: U5.16, X3.D-
USB_D-3: U7.16, X4.D-
USB_D-4: U9.16, X5.D-
USB_D-5: U11.16, X6.D-
USB_D-6: U13.16, X7.D-
USB_D-7: U15.16, X8.D-
USB_D-8: U17.16, X9.D-
USB_D-9: U19.16, X10.D-
USB_D-10: U21.16, X11.D-
USB_D-11: U23.16, X12.D-
USB_D-12: U25.16, X13.D-
USB_D-13: U27.16, X14.D-
USB_D-14: U29.16, X15.D-
USB_D-15: U31.16, X16.D-
USB_D-16: U33.16, X17.D-
USB_D-17: U35.16, X18.D-
USB_D-18: U37.16, X19.D-
USB_D-19: U39.16, X20.D-
USB_D-20: U41.16, X21.D-
USB_D-21: U43.16, X22.D-
USB_D-22: U45.16, X23.D-
USB_D-23: U47.16, X24.D-
USB_D-24: U49.16, X25.D-
USB_D-25: U51.16, X26.D-
USB_D-26: U53.16, X27.D-
USB_D-27: U55.16, X28.D-
USB_D-28: U57.16, X29.D-
USB_D-29: U59.16, X30.D-
VCC: C2.1, C3.1, C5.A, F1.2, R1.2, R2.2, SJ2.2, U1.20, U2.8
VCC1: C4.1, C6.A, C8.1, F2.2, R5.2, R6.2, SJ1.2, U3.20, U4.8
VCC2: C9.1, C10.A, C12.1, F3.2, R9.2, R10.2, SJ3.2, U5.20, U6.8
VCC3: C13.1, C14.A, C16.1, F4.2, R13.2, R14.2, SJ4.2, U7.20, U8.8
VCC4: C17.1, C18.A, C20.1, F5.2, R17.2, R18.2, SJ5.2, U9.20, U10.8
VCC5: C21.1, C22.A, C24.1, F6.2, R21.2, R22.2, SJ6.2, U11.20, U12.8
VCC6: C25.1, C26.A, C28.1, F7.2, R25.2, R26.2, SJ7.2, U13.20, U14.8
VCC7: C29.1, C30.A, C32.1, F8.2, R29.2, R30.2, SJ8.2, U15.20, U16.8
VCC8: C33.1, C34.A, C36.1, F9.2, R33.2, R34.2, SJ9.2, U17.20, U18.8
VCC9: C37.1, C38.A, C40.1, F10.2, R37.2, R38.2, SJ10.2, U19.20, U20.8
VCC10: C41.1, C42.A, C44.1, F11.2, R41.2, R42.2, SJ11.2, U21.20, U22.8
VCC11: C45.1, C46.A, C48.1, F12.2, R45.2, R46.2, SJ12.2, U23.20, U24.8
VCC12: C49.1, C50.A, C52.1, F13.2, R49.2, R50.2, SJ13.2, U25.20, U26.8
VCC13: C53.1, C54.A, C56.1, F14.2, R53.2, R54.2, SJ14.2, U27.20, U28.8
VCC14: C57.1, C58.A, C60.1, F15.2, R57.2, R58.2, SJ15.2, U29.20, U30.8
VCC15: C61.1, C62.A, C64.1, F16.2, R61.2, R62.2, SJ16.2, U31.20, U32.8
VCC16: C65.1, C66.A, C68.1, F17.2, R65.2, R66.2, SJ17.2, U33.20, U34.8
VCC17: C69.1, C70.A, C72.1, F18.2, R69.2, R70.2, SJ18.2, U35.20, U36.8
VCC18: C73.1, C74.A, C76.1, F19.2, R73.2, R74.2, SJ19.2, U37.20, U38.8
VCC19: C77.1, C78.A, C80.1, F20.2, R77.2, R78.2, SJ20.2, U39.20, U40.8
VCC20: C81.1, C82.A, C84.1, F21.2, R81.2, R82.2, SJ21.2, U41.20, U42.8
VCC21: C85.1, C86.A, C88.1, F22.2, R85.2, R86.2, SJ22.2, U43.20, U44.8
VCC22: C89.1, C90.A, C92.1, F23.2, R89.2, R90.2, SJ23.2, U45.20, U46.8
VCC23: C93.1, C94.A, C96.1, F24.2, R93.2, R94.2, SJ24.2, U47.20, U48.8
VCC24: C97.1, C98.A, C100.1, F25.2, R97.2, R98.2, SJ25.2, U49.20, U50.8
VCC25: C101.1, C102.A, C104.1, F26.2, R101.2, R102.2, SJ26.2, U51.20, U52.8
VCC26: C105.1, C106.A, C108.1, F27.2, R105.2, R106.2, SJ27.2, U53.20, U54.8
VCC27: C109.1, C110.A, C112.1, F28.2, R109.2, R110.2, SJ28.2, U55.20, U56.8
VCC28: C113.1, C114.A, C116.1, F29.2, R113.2, R114.2, SJ29.2, U57.20, U58.8
VCC29: C117.1, C118.A, C120.1, F30.2, R117.2, R118.2, SJ30.2, U59.20, U60.8
VCCIO: SJ2.1, U1.4
VCCIO1: SJ1.1, U3.4
VCCIO2: SJ3.1, U5.4
VCCIO3: SJ4.1, U7.4
VCCIO4: SJ5.1, U9.4
VCCIO5: SJ6.1, U11.4
VCCIO6: SJ7.1, U13.4
VCCIO7: SJ8.1, U15.4
VCCIO8: SJ9.1, U17.4
VCCIO9: SJ10.1, U19.4
VCCIO10: SJ11.1, U21.4
VCCIO11: SJ12.1, U23.4
VCCIO12: SJ13.1, U25.4
VCCIO13: SJ14.1, U27.4
VCCIO14: SJ15.1, U29.4
VCCIO15: SJ16.1, U31.4
VCCIO16: SJ17.1, U33.4
VCCIO17: SJ18.1, U35.4
VCCIO18: SJ19.1, U37.4
VCCIO19: SJ20.1, U39.4
VCCIO20: SJ21.1, U41.4
VCCIO21: SJ22.1, U43.4
VCCIO22: SJ23.1, U45.4
VCCIO23: SJ24.1, U47.4
VCCIO24: SJ25.1, U49.4
VCCIO25: SJ26.1, U51.4
VCCIO26: SJ27.1, U53.4
VCCIO27: SJ28.1, U55.4
VCCIO28: SJ29.1, U57.4
VCCIO29: SJ30.1, U59.4

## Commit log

2015-05-06 Adding hardware files, readme
2015-10-16 created new panel v11

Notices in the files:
parts and their libraries:
SparkFun: Released under the Creative Commons Attribution Share-Alike 3.0 License
SparkFun: http://creativecommons.org/licenses/by-sa/3.0
SparkFun-Aesthetics: Licensing: CC v3.0 Share-Alike You are welcome to use this library for commercial purposes.
